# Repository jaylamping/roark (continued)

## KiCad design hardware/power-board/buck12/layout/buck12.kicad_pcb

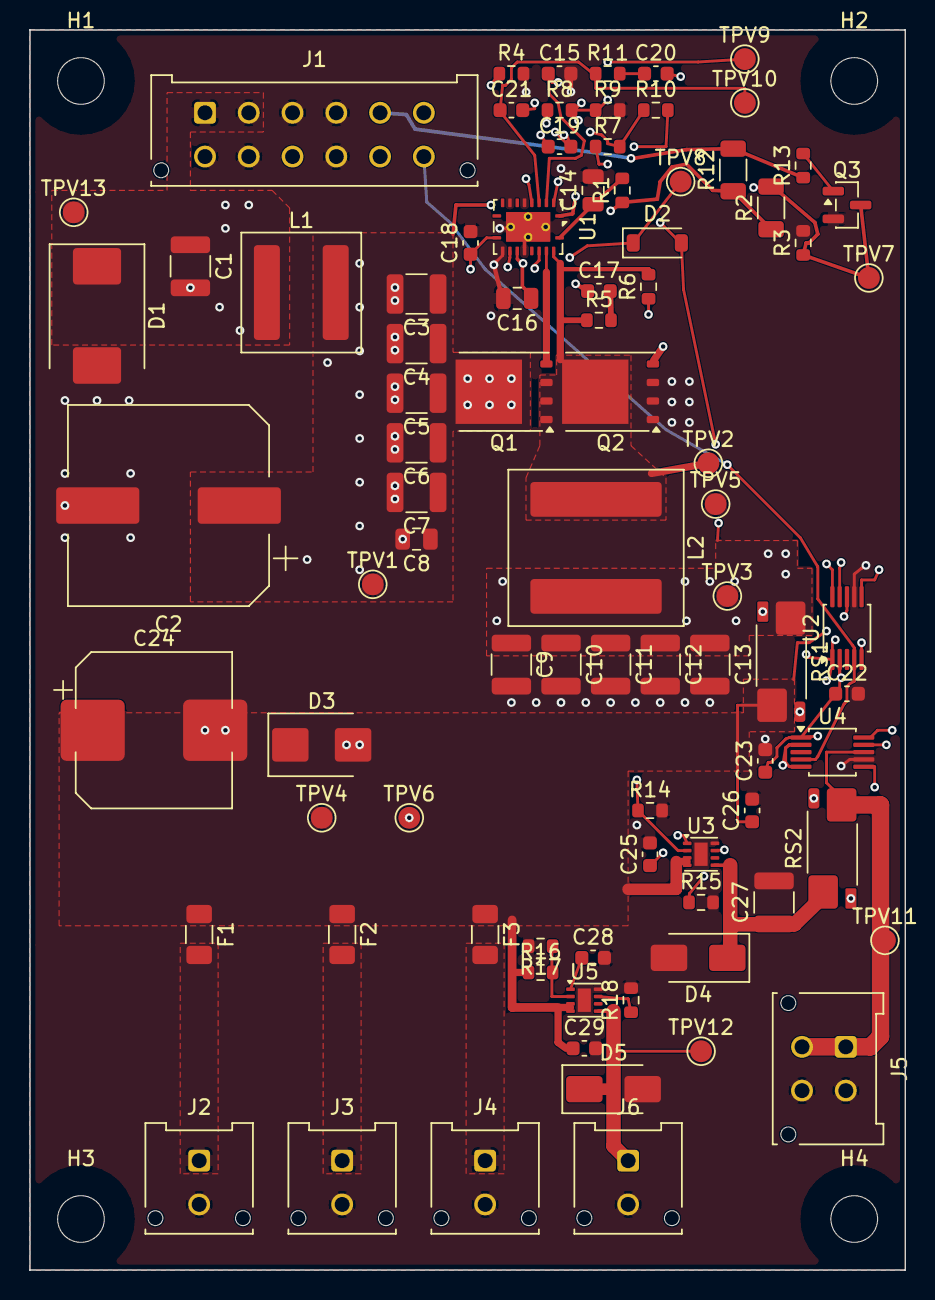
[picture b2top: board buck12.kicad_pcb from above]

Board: 6 copper layers, 60.0 x 85.0 mm, 90 parts (0 on the bottom side), 42 nets.

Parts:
C1: 1uF 100V X7R; C_1210_3225Metric
C2: 47uF 100V EMVH101ARA470MKE0S; CP_Elec_12.5x13.5_ChemiCon
C3, C4, C5, C6, C7: 2.2uF 100V X7R; C_1210_3225Metric
C8, C14: 100nF 100V X7R; C_0805_2012Metric
C9, C10, C11, C12, C13, C27: 22uF 25V X7R; C_1210_3225Metric
C15: 47nF X7R; C_0603_1608Metric
C16: 2.2uF 25V X7R; C_0805_2012Metric
C17, C22, C23, C26, C29: 100nF 50V X7R; C_0603_1608Metric
C18: 18pF 100V C0G; C_0603_1608Metric
C19: 1nF C0G; C_0603_1608Metric
C20: 4.7nF C0G; C_0603_1608Metric
C21: 10pF C0G; C_0603_1608Metric
C24: 330uF 25V EEH-ZA1E331V; CP_Elec_10x10.5_ZA
C25, C28: 3.3nF C0G; C_0603_1608Metric
D1: SK810L-TP; D_SMC
D2: BAT46W; D_SOD-123
D3: SMBJ12A; D_SMB
D4, D5: B340A-13-F; D_SMA
F1, F2: 5A 32V 0466005; Fuse_1206_3216Metric
F3: 2A 32V 0466002; Fuse_1206_3216Metric
H1, H2, H3, H4: M3; MountingHole_3.2mm_M3
J1: J24 mate: 1-2 +VIN, 3-4 GND, 5 ON/OFF (low = on),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; Molex_Micro-Fit_3.0_43045-1212_2x06_P3.00mm_Vertical
J2: 12 V to Jetson (fused); Molex_Micro-Fit_3.0_43045-0212_2x01_P3.00mm_Vertical
J3: 12 V to Pi 5 V buck (fused); Molex_Micro-Fit_3.0_43045-0212_2x01_P3.00mm_Vertical
J4: 12 V to fans (fused); Molex_Micro-Fit_3.0_43045-0212_2x01_P3.00mm_Vertical
J5: SPARE_SW, off with the motors (2 x 2, keyed apart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; Molex_Micro-Fit_3.0_43045-0412_2x02_P3.00mm_Vertical
J6: SPARE_ON, always on; Molex_Micro-Fit_3.0_43045-0212_2x01_P3.00mm_Vertical
L1: 2.2uH XAL7030-222MEC; L_Coilcraft_XAL7030-222
L2: 6.8uH XAL1010-682MED; L_Coilcraft_XAL1010-XXX
Q1: BSC070N10NS5ATMA1; TDSON-8-1
Q2: BSC040N10NS5ATMA1; TDSON-8-1
Q3: MMBT3904; SOT-23
R1, R5: 2.2R; R_0603_1608Metric
R2: 300k 1%; R_1206_3216Metric
R3: 12.4k 1%; R_0603_1608Metric
R4: 24.9k 1%; R_0603_1608Metric
R6: 330R 1%; R_0603_1608Metric
R7: 0R (loop injection); R_0603_1608Metric
R8: 21k 1%; R_0603_1608Metric
R9: 1.5k 1%; R_0603_1608Metric
R10: 100R; R_0603_1608Metric
R11: 8.06k 1%; R_0603_1608Metric
R12: 220k; R_1206_3216Metric
R13: 10k; R_0603_1608Metric
R14: 68k; R_0603_1608Metric
R15: 499R 1%; R_0603_1608Metric
R16: 100k; R_0603_1608Metric
R17: 33k; R_0603_1608Metric
R18: 1.02k 1%; R_0603_1608Metric
RS1: 2mR 2512 Kelvin WSK25122L000FEA; R_Shunt_Vishay_WSK2512_6332Metric_T1.19mm
RS2: 5mR 2512 Kelvin WSK25125L000FEA; R_Shunt_Vishay_WSK2512_6332Metric_T1.19mm
TPV1: TP VIN; TestPoint_Pad_D1.5mm
TPV2: TP SW; TestPoint_Pad_D1.5mm
TPV3: TP VOUT; TestPoint_Pad_D1.5mm
TPV4: TP +12V; TestPoint_Pad_D1.5mm
TPV5, TPV6: TP GND; TestPoint_Pad_D1.5mm
TPV7: TP EN; TestPoint_Pad_D1.5mm
TPV8: TP VCC; TestPoint_Pad_D1.5mm
TPV9: TP SS; TestPoint_Pad_D1.5mm
TPV10: TP COMP; TestPoint_Pad_D1.5mm
TPV11: TP SPARE_SW; TestPoint_Pad_D1.5mm
TPV12: TP SPARE_ON; TestPoint_Pad_D1.5mm
TPV13: TP VIN_P; TestPoint_Pad_D1.5mm
U1: LM5146RGYR; Texas_RGY_R-PVQFN-N20_EP2.05x3.05mm_ThermalVias_0.3mm
U2, U4: INA237AIDGSR; TSSOP-10_3x3mm_P0.5mm
U3, U5: TPS259541DSGR; Texas_DSG0008A_WSON-8-1EP_2x2mm_P0.5mm_EP0.9x1.6mm

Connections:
/+3V3_PI: C22.1, C23.1, J1.6, U2.2, U2.6, U4.1, U4.6
/+12V: C24.1, C26.1, C29.1, D3.1, F1.1, F2.1, F3.1, R16.1, RS1.4, TPV4.1, U2.8, U3.3, U3.4, U5.3, U5.4
/+12V_FAN: F3.2, J4.1
/+12V_JET: F1.2, J2.1
/+12V_PI: F2.2, J3.1
/BST: C17.1, U1.17
/BST_R: C17.2, R5.2
/COMP: C21.1, R11.1, TPV10.1, U1.4
/COMP_Z: C20.1, R11.2
/EN: Q3.3, R2.2, R3.1, TPV7.1, U1.1
/FB: C19.2, C20.2, C21.2, R8.2, R9.1, U1.5
/FB_Z: C19.1, R10.2
/HO: Q1.4, U1.18
/I2C_SCL: J1.11, U2.1, U2.5, U4.2, U4.5
/I2C_SDA: J1.12, U2.4, U4.4
/ILIM: C18.1, R6.1, U1.11
/LO: Q2.4, U1.13
/ON_B: Q3.1, R13.2
/ON_N: J1.5, R12.2, R13.1
/RT: R4.1, U1.2
/SH12_N: RS1.3, U2.9
/SH12_P: RS1.2, U2.10
/SHSP_N: RS2.3, U4.9
/SHSP_P: RS2.2, U4.10
/SPARE_ON: D5.1, J6.1, TPV12.1, U5.5
/SPARE_SW: J5.1, J5.3, RS2.4, TPV11.1, U4.8
/SPON_DV: C28.1, U5.1
/SPON_EN: R16.2, R17.1, U5.2
/SPON_ILM: R18.1, U5.7
/SP_DV: C25.1, U3.1
/SP_EN: J1.9, R14.1, U3.2
/SP_ILM: R15.1, U3.7
/SP_SW1: C27.1, D4.1, RS2.1, U3.5
/SS: C15.1, TPV9.1, U1.3
/SW: L2.1, Q1.1, Q1.2, Q1.3, Q2.5, R5.1, R6.2, TPV2.1, U1.19
/VCC: C16.1, D2.1, TPV8.1, U1.14
/VIN: C2.1, C3.1, C4.1, C5.1, C6.1, C7.1, C8.1, L1.2, Q1.5, R1.1, R2.1, R12.1, TPV1.1
/VIN_C: C14.1, R1.2, U1.20
/VIN_P: C1.1, D1.1, J1.1, J1.2, L1.1, TPV13.1
/VOUT: C9.1, C10.1, C11.1, C12.1, C13.1, D2.2, L2.2, R7.1, RS1.1, TPV3.1
/VOUT_S: R7.2, R8.1, R10.1
GND: C1.2, C2.2, C3.2, C4.2, C5.2, C6.2, C7.2, C8.2, C9.2, C10.2, C11.2, C12.2, C13.2, C14.2, C15.2, C16.2, C18.2, C22.2, C23.2, C24.2, C25.2, C26.2, C27.2, C28.2, C29.2, D1.2, D3.2, D4.2, D5.2, J1.3, J1.4, J1.7, J1.8, J1.10, J2.2, J3.2, J4.2, J5.2, J5.4, J6.2, Q2.1, Q2.2, Q2.3, Q3.2, R3.2, R4.2, R9.2, R14.2, R15.2, R17.2, R18.2, TPV5.1, TPV6.1, U1.6, U1.8, U1.12, U1.15, U1.21, U2.7, U3.8, U3.9, U4.7, U5.8, U5.9

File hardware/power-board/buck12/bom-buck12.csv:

"Refs","Value","Footprint","Qty","DNP"
"C1","1uF 100V X7R","Capacitor_SMD:C_1210_3225Metric","1",""
"C2","47uF 100V EMVH101ARA470MKE0S","buck12:CP_Elec_12.5x13.5_ChemiCon","1",""
"C3,C4,C5,C6,C7","2.2uF 100V X7R","Capacitor_SMD:C_1210_3225Metric","5",""
"C8,C14","100nF 100V X7R","Capacitor_SMD:C_0805_2012Metric","2",""
"C9,C10,C11,C12,C13,C27","22uF 25V X7R","Capacitor_SMD:C_1210_3225Metric","6",""
"C15","47nF X7R","Capacitor_SMD:C_0603_1608Metric","1",""
"C16","2.2uF 25V X7R","Capacitor_SMD:C_0805_2012Metric","1",""
"C17,C22,C23,C26,C29","100nF 50V X7R","Capacitor_SMD:C_0603_1608Metric","5",""
"C18","18pF 100V C0G","Capacitor_SMD:C_0603_1608Metric","1",""
"C19","1nF C0G","Capacitor_SMD:C_0603_1608Metric","1",""
"C20","4.7nF C0G","Capacitor_SMD:C_0603_1608Metric","1",""
"C21","10pF C0G","Capacitor_SMD:C_0603_1608Metric","1",""
"C24","330uF 25V EEH-ZA1E331V","buck12:CP_Elec_10x10.5_ZA","1",""
"C25,C28","3.3nF C0G","Capacitor_SMD:C_0603_1608Metric","2",""
"D1","SK810L-TP","Diode_SMD:D_SMC","1",""
"D2","BAT46W","Diode_SMD:D_SOD-123","1",""
"D3","SMBJ12A","Diode_SMD:D_SMB","1",""
"D4,D5","B340A-13-F","Diode_SMD:D_SMA","2",""
"F1,F2","5A 32V 0466005","Fuse:Fuse_1206_3216Metric","2",""
"F3","2A 32V 0466002","Fuse:Fuse_1206_3216Metric","1",""
"J1","J24 mate: 1-2 +VIN, 3-4 GND, 5 ON/OFF (low = on), 6 +3V3_PI, 7-8 GND, 9 SP_EN, 10 GND, 11 SCL, 12 SDA","Connector_Molex:Molex_Micro-Fit_3.0_43045-1212_2x06_P3.00mm_Vertical","1",""
"J2","12 V to Jetson (fused)","Connector_Molex:Molex_Micro-Fit_3.0_43045-0212_2x01_P3.00mm_Vertical","1",""
"J3","12 V to Pi 5 V buck (fused)","Connector_Molex:Molex_Micro-Fit_3.0_43045-0212_2x01_P3.00mm_Vertical","1",""
"J4","12 V to fans (fused)","Connector_Molex:Molex_Micro-Fit_3.0_43045-0212_2x01_P3.00mm_Vertical","1",""
"J5","SPARE_SW, off with the motors (2 x 2, keyed apart from the 2-pin outputs)","Connector_Molex:Molex_Micro-Fit_3.0_43045-0412_2x02_P3.00mm_Vertical","1",""
"J6","SPARE_ON, always on","Connector_Molex:Molex_Micro-Fit_3.0_43045-0212_2x01_P3.00mm_Vertical","1",""
"L1","2.2uH XAL7030-222MEC","Inductor_SMD:L_Coilcraft_XAL7030-222","1",""
"L2","6.8uH XAL1010-682MED","Inductor_SMD:L_Coilcraft_XAL1010-XXX","1",""
"Q1","BSC070N10NS5ATMA1","Package_TO_SOT_SMD:TDSON-8-1","1",""
"Q2","BSC040N10NS5ATMA1","Package_TO_SOT_SMD:TDSON-8-1","1",""
"Q3","MMBT3904","Package_TO_SOT_SMD:SOT-23","1",""
"R1,R5","2.2R","Resistor_SMD:R_0603_1608Metric","2",""
"R2","300k 1%","Resistor_SMD:R_1206_3216Metric","1",""
"R3","12.4k 1%","Resistor_SMD:R_0603_1608Metric","1",""
"R4","24.9k 1%","Resistor_SMD:R_0603_1608Metric","1",""
"R6","330R 1%","Resistor_SMD:R_0603_1608Metric","1",""
"R7","0R (loop injection)","Resistor_SMD:R_0603_1608Metric","1",""
"R8","21k 1%","Resistor_SMD:R_0603_1608Metric","1",""
"R9","1.5k 1%","Resistor_SMD:R_0603_1608Metric","1",""
"R10","100R","Resistor_SMD:R_0603_1608Metric","1",""
"R11","8.06k 1%","Resistor_SMD:R_0603_1608Metric","1",""
"R12","220k","Resistor_SMD:R_1206_3216Metric","1",""
"R13","10k","Resistor_SMD:R_0603_1608Metric","1",""
"R14","68k","Resistor_SMD:R_0603_1608Metric","1",""
"R15","499R 1%","Resistor_SMD:R_0603_1608Metric","1",""
"R16","100k","Resistor_SMD:R_0603_1608Metric","1",""
"R17","33k","Resistor_SMD:R_0603_1608Metric","1",""
"R18","1.02k 1%","Resistor_SMD:R_0603_1608Metric","1",""
"RS1","2mR 2512 Kelvin WSK25122L000FEA","Resistor_SMD:R_Shunt_Vishay_WSK2512_6332Metric_T1.19mm","1",""
"RS2","5mR 2512 Kelvin WSK25125L000FEA","Resistor_SMD:R_Shunt_Vishay_WSK2512_6332Metric_T1.19mm","1",""
"U1","LM5146RGYR","Package_DFN_QFN:Texas_RGY_R-PVQFN-N20_EP2.05x3.05mm_ThermalVias","1",""
"U2,U4","INA237AIDGSR","Package_SO:TSSOP-10_3x3mm_P0.5mm","2",""
"U3,U5","TPS259541DSGR","Package_SON:Texas_DSG0008A_WSON-8-1EP_2x2mm_P0.5mm_EP0.9x1.6mm","2",""

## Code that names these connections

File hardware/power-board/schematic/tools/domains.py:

"""Net classes for the rev B5 spacing rules (LAYOUT_RULES.md), shared by tools/grid_route.py (plain Python) and
tools/route_checks.py / hv_spacing.py / gnd_fanout.py (KiCad's Python), so the router routes to the rules the checks test.
  - 54 V copper (HV): LAYOUT_RULES.md's list (BAT, SW_D, MID, VBUS, ABS, CL_D, BRK_*, SH*, V_L*) plus ABS_N and the
    port drains D_L*, and U8's supply and sense pins VS_A, CSP_A, CSN_A (on RS1's pads through 0R; added 2026-11-10,
    no copper had to move). The latch's own supply chain (BAT_F, BAT_R, BAT_CTL) and the divider taps are not in it.
  - E-stop safety nets (ESTOP): keep >= 1.5 mm to 54 V copper (the HV list) on every layer, 0.6 mm (outer) to copper
    riding on 54 V (0.44 MOhm of leakage into UVLO enables bank
    B by itself).
  - Voltage domains: copper that rides on one 54 V node (a port's gate and bootstrap on its V_L, sense taps on VBUS, bank
    B's gate on MID, ...). Pairs inside one domain are tens of volts apart at most, so the 0.6 mm rule (outer layers,
    IPC-2221B B2, 51-100 V) applies only between different domains where one side is 54 V.
"""
import re
ESTOP_NAMES='RUN RUN_A RUN_B RUN_P SP_ENR SP_EN UVLO EN_A FLT_A FLT_D L_B L_E L_PB L_PC MID_B VB_B INT_B WDO_N VWD'.split()
def is_estop(n): return n in {'/'+x for x in ESTOP_NAMES} or bool(re.match(r'/(LOOP_|RST_)',n))
import os
# PB_HV_EXTRA=BAT_F,BAT_CTL,...: a what-if for tools/route_checks.py, treating these nets as 54 V copper too
HV_EXTRA={'/'+x for x in os.environ.get('PB_HV_EXTRA','').split(',') if x}
# PB_ESTOP_GAP=1.7: the E-stop-to-54 V distance the routers keep (default the rule, 1.5 mm); the buck board's build
# keeps 1.7 mm (buck12/tools/hv_buck.py SP_MIN)
ESTOP_GAP=float(os.environ.get('PB_ESTOP_GAP','1.5'))
def is_hv(n):
    return (bool(re.match(r'/(BAT|SW_D|MID|VBUS|ABS|ABS_N|CL_D|VS_A|CSP_A|CSN_A)$|/(BRK_|SH|V_L|D_L)',n)) or n in HV_EXTRA) and not is_estop(n) and not n.startswith('/SH12')
DOMRE=[('BAT',r'/(BAT|SW_D|SH_[PN]|SH9_[PN]|BRK_D|CSP_A|CSN_A|VS_A)$'),('MID',r'/(MID|GA1|GA2|GATE_A|BST_A|G1PD_A)$'),
       ('VBUS',r'/(VBUS|D_L\d|CSP_L\d|INP_L\d|SHL\d_[PN]|G1|G2|GATE|SHSP_[PN])$'),('ABS',r'/ABS$'),('CLD',r'/CL_D$'),
       ('BRK',r'/BRK_(F|P|T|PG|IN|GATE|G1)$')]+[(f'VL{k}',rf'/(V|G|GPD|GPU|BST|GC)_L{k}$') for k in range(1,7)]
def dom(n):
    """domain name of a net, or None for ground-referenced copper"""
    for name,rx in DOMRE:
        if re.match(rx,n): return name
    return None
def rides(n):
    """54 V copper, or copper riding on a 54 V node (a gate or bootstrap on its source, a sense tap on VBUS)"""
    return is_hv(n) or dom(n) is not None
# The latch's own 54 V supply chain (BAT -> F1 -> BAT_F -> 22R -> BAT_R -> ES1D -> BAT_CTL -> U2) lies at the latch
# block, so it is not on the 54 V list (the fail-safe E-stop nets may pass it at 0.2 mm). These E-stop nets are the ones
# that leakage from 54 V could push toward "run" at over 100 kOhm (LAYOUT_RULES.md, "Leakage from the latch supply": the
# table net by net), and they keep 1.5 mm to the chain on every layer:
#   L_B, RST_C  0.47-0.56 MOhm turns the seal-in NPN on: the latch sets without a reset press
#   MID_B       20 MOhm reports "MID healthy" and releases the reset interlock
#   RUN_A, EN_A 4.3 MOhm enables bank A;  RUN_B, UVLO, FLT_D  0.44-0.7 MOhm enables bank B
#   RUN         48 kOhm sets the latch, 10 kOhm holds both banks on with the loop open
#   LOOP_RET    43 kOhm keeps the latch set through a press, 9 kOhm both banks
#   SP_ENR, SP_EN  about 1.5 / 3 MOhm turns SPARE_SW on (the buck board's U3 EN, 68 kOhm pull-down) during an E-stop
# tools/latch_block.py places the chain and L_B's parts so that this holds; clearance() gives the routers and
# tools/route_checks.py the 1.5 mm, the .kicad_dru rule latch_supply_leak (leak_rule() below; tools/handfinish_prep.py
# writes it, tools/check.py compares) gives it to KiCad's DRC and fill, and route_checks check 10 counts the pairs: 0.
LATCH_SUPPLY={'/BAT_F','/BAT_R','/BAT_CTL'}
LEAK_SENSITIVE={'/L_B','/RST_C','/MID_B','/RUN_A','/EN_A','/RUN_B','/UVLO','/FLT_D','/RUN','/LOOP_RET','/SP_ENR','/SP_EN'}
LEAK_PAIRS_MAX=0
def leak_rule():
    """the .kicad_dru rule for the two lists, exactly as tools/handfinish_prep.py writes it"""
    sup=' || '.join(f"A.NetName == '{n}'" for n in sorted(LATCH_SUPPLY)); sen=' || '.join(f"B.NetName == '{n}'" for n in sorted(LEAK_SENSITIVE))
    return f'(rule latch_supply_leak\n  (constraint clearance (min 1.5mm))\n  (condition "({sup}) && ({sen})"))\n'
def latch_leak(a,b):
    """one net on the latch's supply chain, the other a leakage-sensitive E-stop net"""
    return (a in LATCH_SUPPLY and b in LEAK_SENSITIVE) or (b in LATCH_SUPPLY and a in LEAK_SENSITIVE)
# The latch block (tools/place.py, option A), floorplan mm (X0, X1, Y0, Y1). LAYOUT_RULES: no 54 V copper on L2-L5 under
# it, so no 54 V inner track or via there. latch_page() gives KiCad page mm (place.py: page X = X + 150, page Y = 440 - Y).
LATCH=(-48.0,-31.0,254.0,310.5)
def latch_page():
    X0,X1,Y0,Y1=LATCH; return (X0+150,X1+150,440-Y1,440-Y0)
def latch_inner_banned(n):
    """copper that may not be on an inner layer under the latch block: 54 V, riding on 54 V, or the latch's own supply chain
    (route_checks check 4; the routers hold the same set)"""
    return rides(n) or n in LATCH_SUPPLY
# The VBUS band (page mm X0, X1, Y0, Y1): the 60 A stem's full width between the bank FETs and the ports, X 130 to the
# stem's east edge at 169.2. The routers put no via of another net in it; tools/pour_width.py counts the ones there.
VBUS_BAND=(130.0,169.2,180.0,190.0)
def in_vbus_band(p): return VBUS_BAND[0]<=p[0]<=VBUS_BAND[1] and VBUS_BAND[2]<=p[1]<=VBUS_BAND[3]
# The board gets an acrylic conformal coat after bring-up (Joey, 2026-11-09; IPC-2221B Table 6-1, 51-100 V: A5/A7 0.13 mm,
# B4 0.13 mm, against B2 0.6 mm and A6 0.5 mm uncoated), so the 0.6 mm domain rule is the 0.2 mm default. The E-stop
# 1.5 mm rule and the hole keep-outs don't change. PB_COATED=0 checks the bare-board rule.
COATED=os.environ.get('PB_COATED','1')=='1'
def clearance(a,b,outer):
    """required copper clearance (mm) between nets a and b on an outer (True) or inner layer"""
    if a==b: return 0.0
    if (is_estop(a) and is_hv(b)) or (is_estop(b) and is_hv(a)): return ESTOP_GAP   # the rule's net list; 54 V-riding nets get 0.6 below
    if latch_leak(a,b): return 1.5   # the latch supply chain against the leakage-sensitive E-stop nets
    if (rides(a) or rides(b)) and not (dom(a) and dom(a)==dom(b)): return 0.6 if (outer and not COATED) else 0.2
    return 0.2
# Documented exceptions (LAYOUT_RULES.md, "Exceptions and hand-laid copper"), tested by tools/route_checks.py checks 7 and 8.
# Each excepted via is pinned to its coordinates (page mm, VIA_TOL): a via of the same net anywhere else fails.
# Vias of another net inside a MID pour outline: the three VBUS vias at the bank B FETs' pins 2-3 (tools/route_power.py),
# GATE_A's at Q8's gate, GA2's in the pour's dead tip beside U8, and G2's at Q2's gate (the only way out of the slot
# between Q1's tab and Q2's pins; accepted in the project thread on 2026-11-10, to be confirmed at the review).
VIA_TOL=0.05
MID_VIA_OK={'/VBUS':[(151.2,161.46),(151.2,162.73),(132.0,162.73)],'/GATE_A':[(132.0,141.46)],'/GA2':[(167.95,157.0)],'/G2':[(149.9,160.19)]}
# Gate-drive nets (LAYOUT_RULES "Critical nets") take at most 2 vias. GATE_A has 3 from the staged routing: every one of
# its vias must be one of the listed ones. (G2 had 3 until R2 moved to the gate tee, 2026-11-10; it now has 2.)
GATE_RE=r'/((G|GPD|GPU|BST)_L\d|GATE|GATE_A|GA[12]|G[12]|G1PD_A|BST_A|BRK_GATE|BRK_G1|PRE_G|CL_G)$'
GATE_VIAS_MAX=2
GATE_VIA_OK={'/GATE_A':[(132.0,141.46),(168.55,158.85),(168.55,164.75)]}
def via_listed(p,table,net):
    """is the via at p (page mm) one of the net's documented ones?"""
    return any(abs(p[0]-q[0])<=VIA_TOL and abs(p[1]-q[1])<=VIA_TOL for q in table.get(net,()))
# Kelvin pairs: the least share (percent) of both legs' length, measured from the shunt's sense pads to the IC pins
# (tools/route_checks.py check 3), that runs within 1.0 mm (centre to centre, same layer) of the other leg. The floors are
# the routed board's values of 2026-11-10 rounded down: a re-route may not make a pair worse.
# A Kelvin leg ends at IC pins; these parts count as ends too: R61 and R62 are the 0R links from the SH pair into U8's
# CS pins (CSP_A, CSN_A), so the pair's run to them is part of the pair.
KELVIN_ENDS={'/SH_P':('R61',),'/SH_N':('R62',)}
KELVIN_FLOOR={'/SH':86,'/SH9':66,'/SHL1':57,'/SHL2':57,'/SHL3':57,'/SHL4':57,'/SHL5':57,'/SHL6':57}
